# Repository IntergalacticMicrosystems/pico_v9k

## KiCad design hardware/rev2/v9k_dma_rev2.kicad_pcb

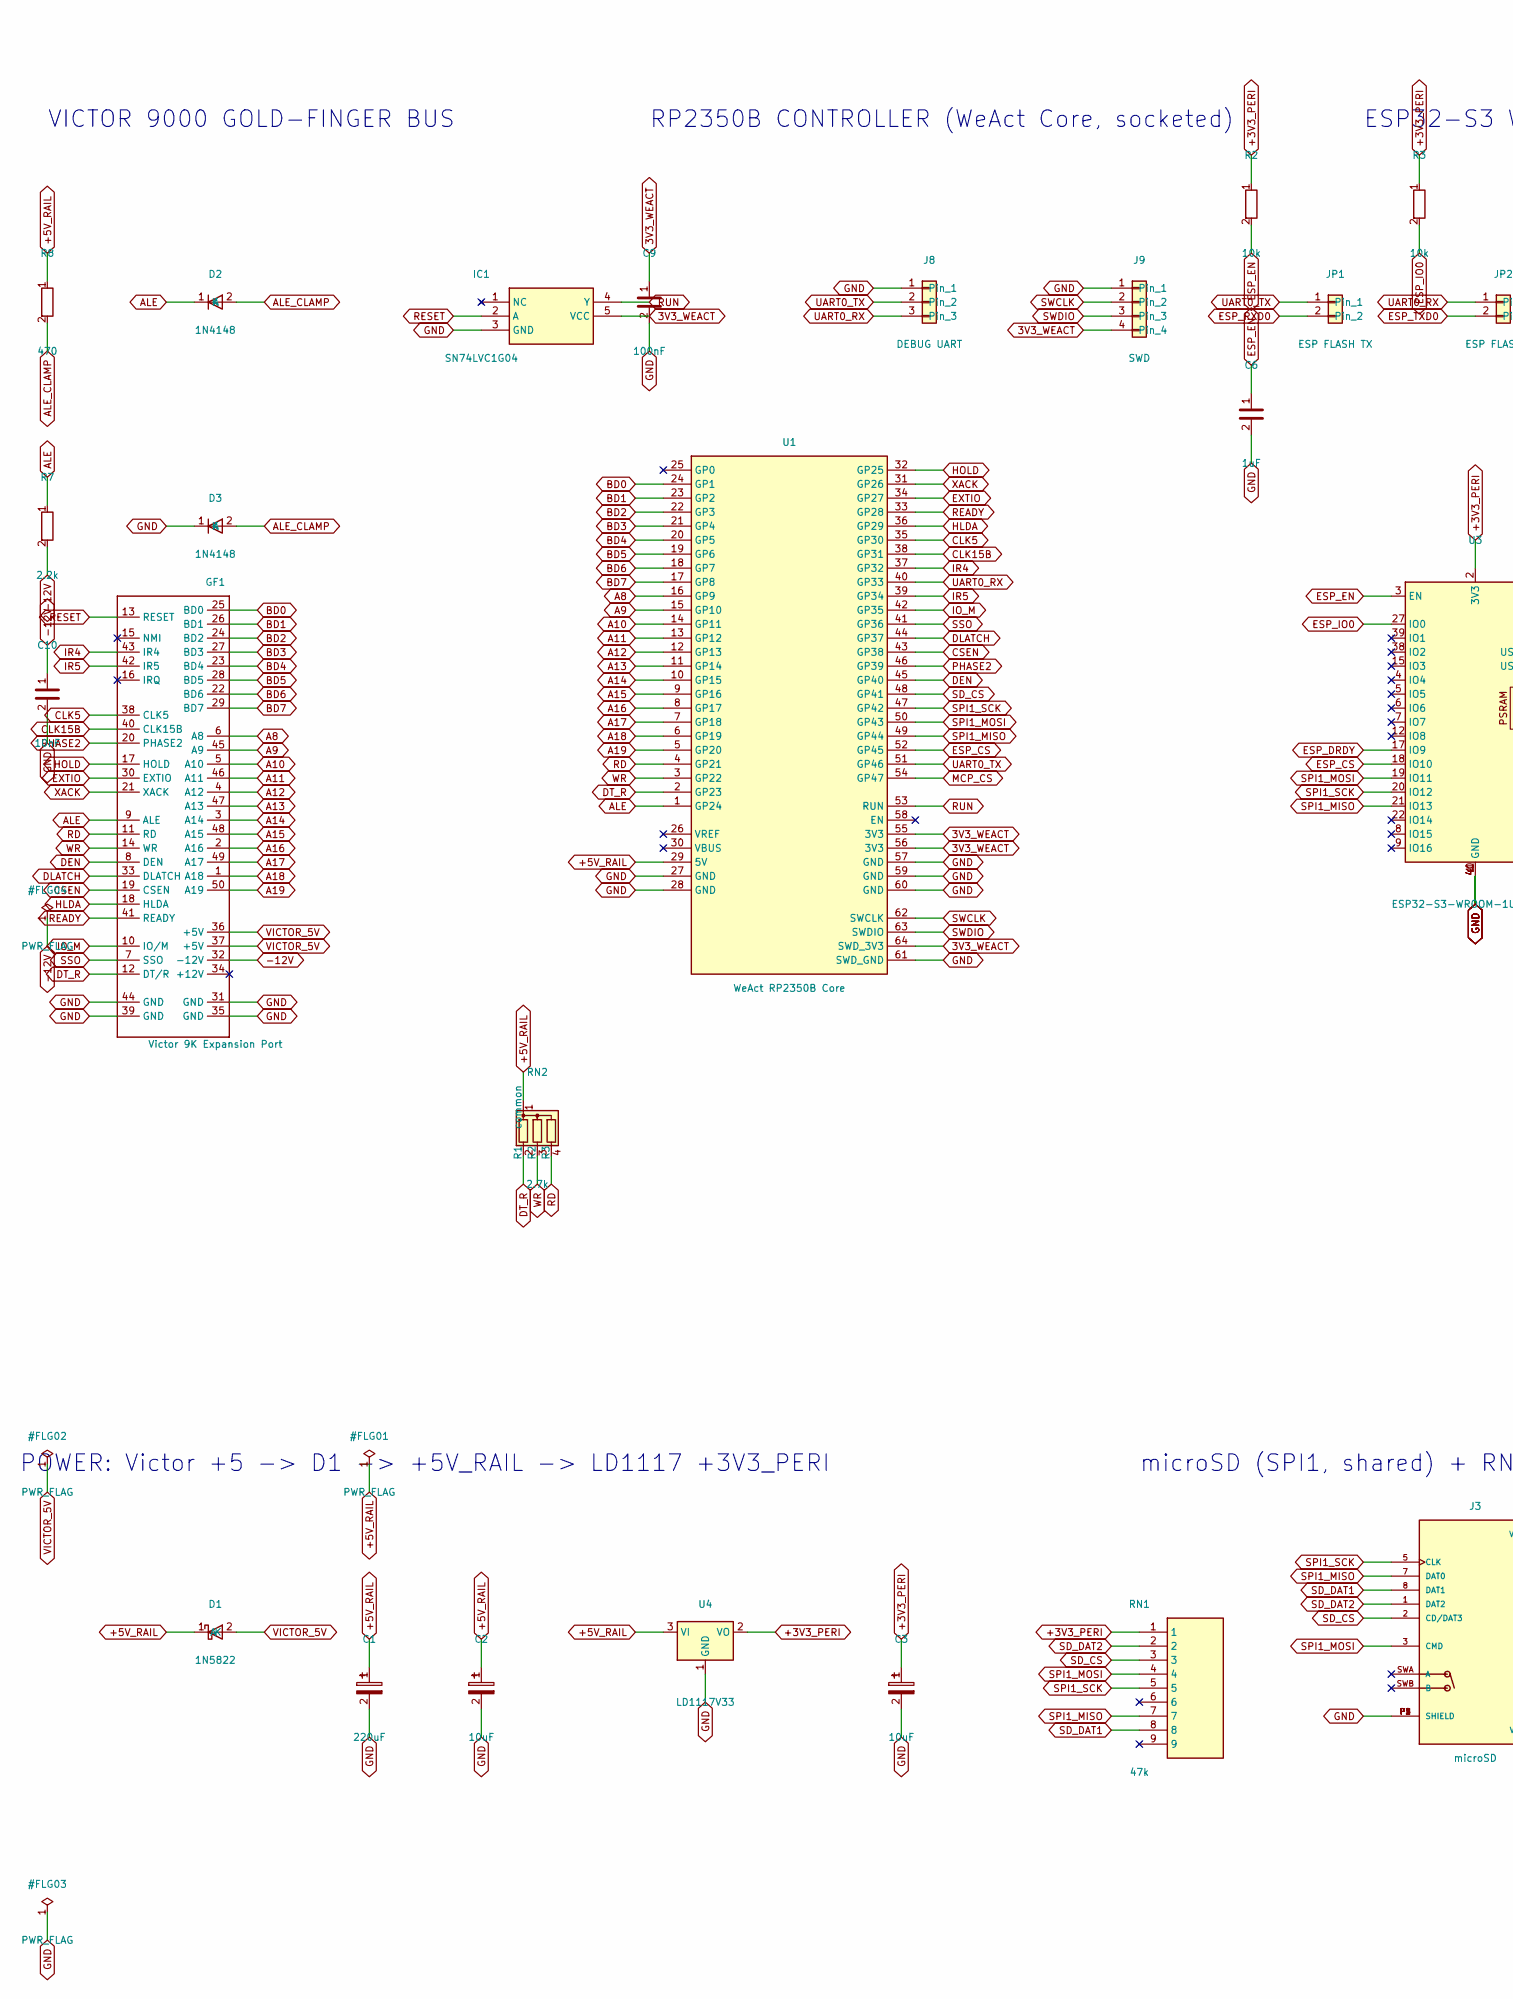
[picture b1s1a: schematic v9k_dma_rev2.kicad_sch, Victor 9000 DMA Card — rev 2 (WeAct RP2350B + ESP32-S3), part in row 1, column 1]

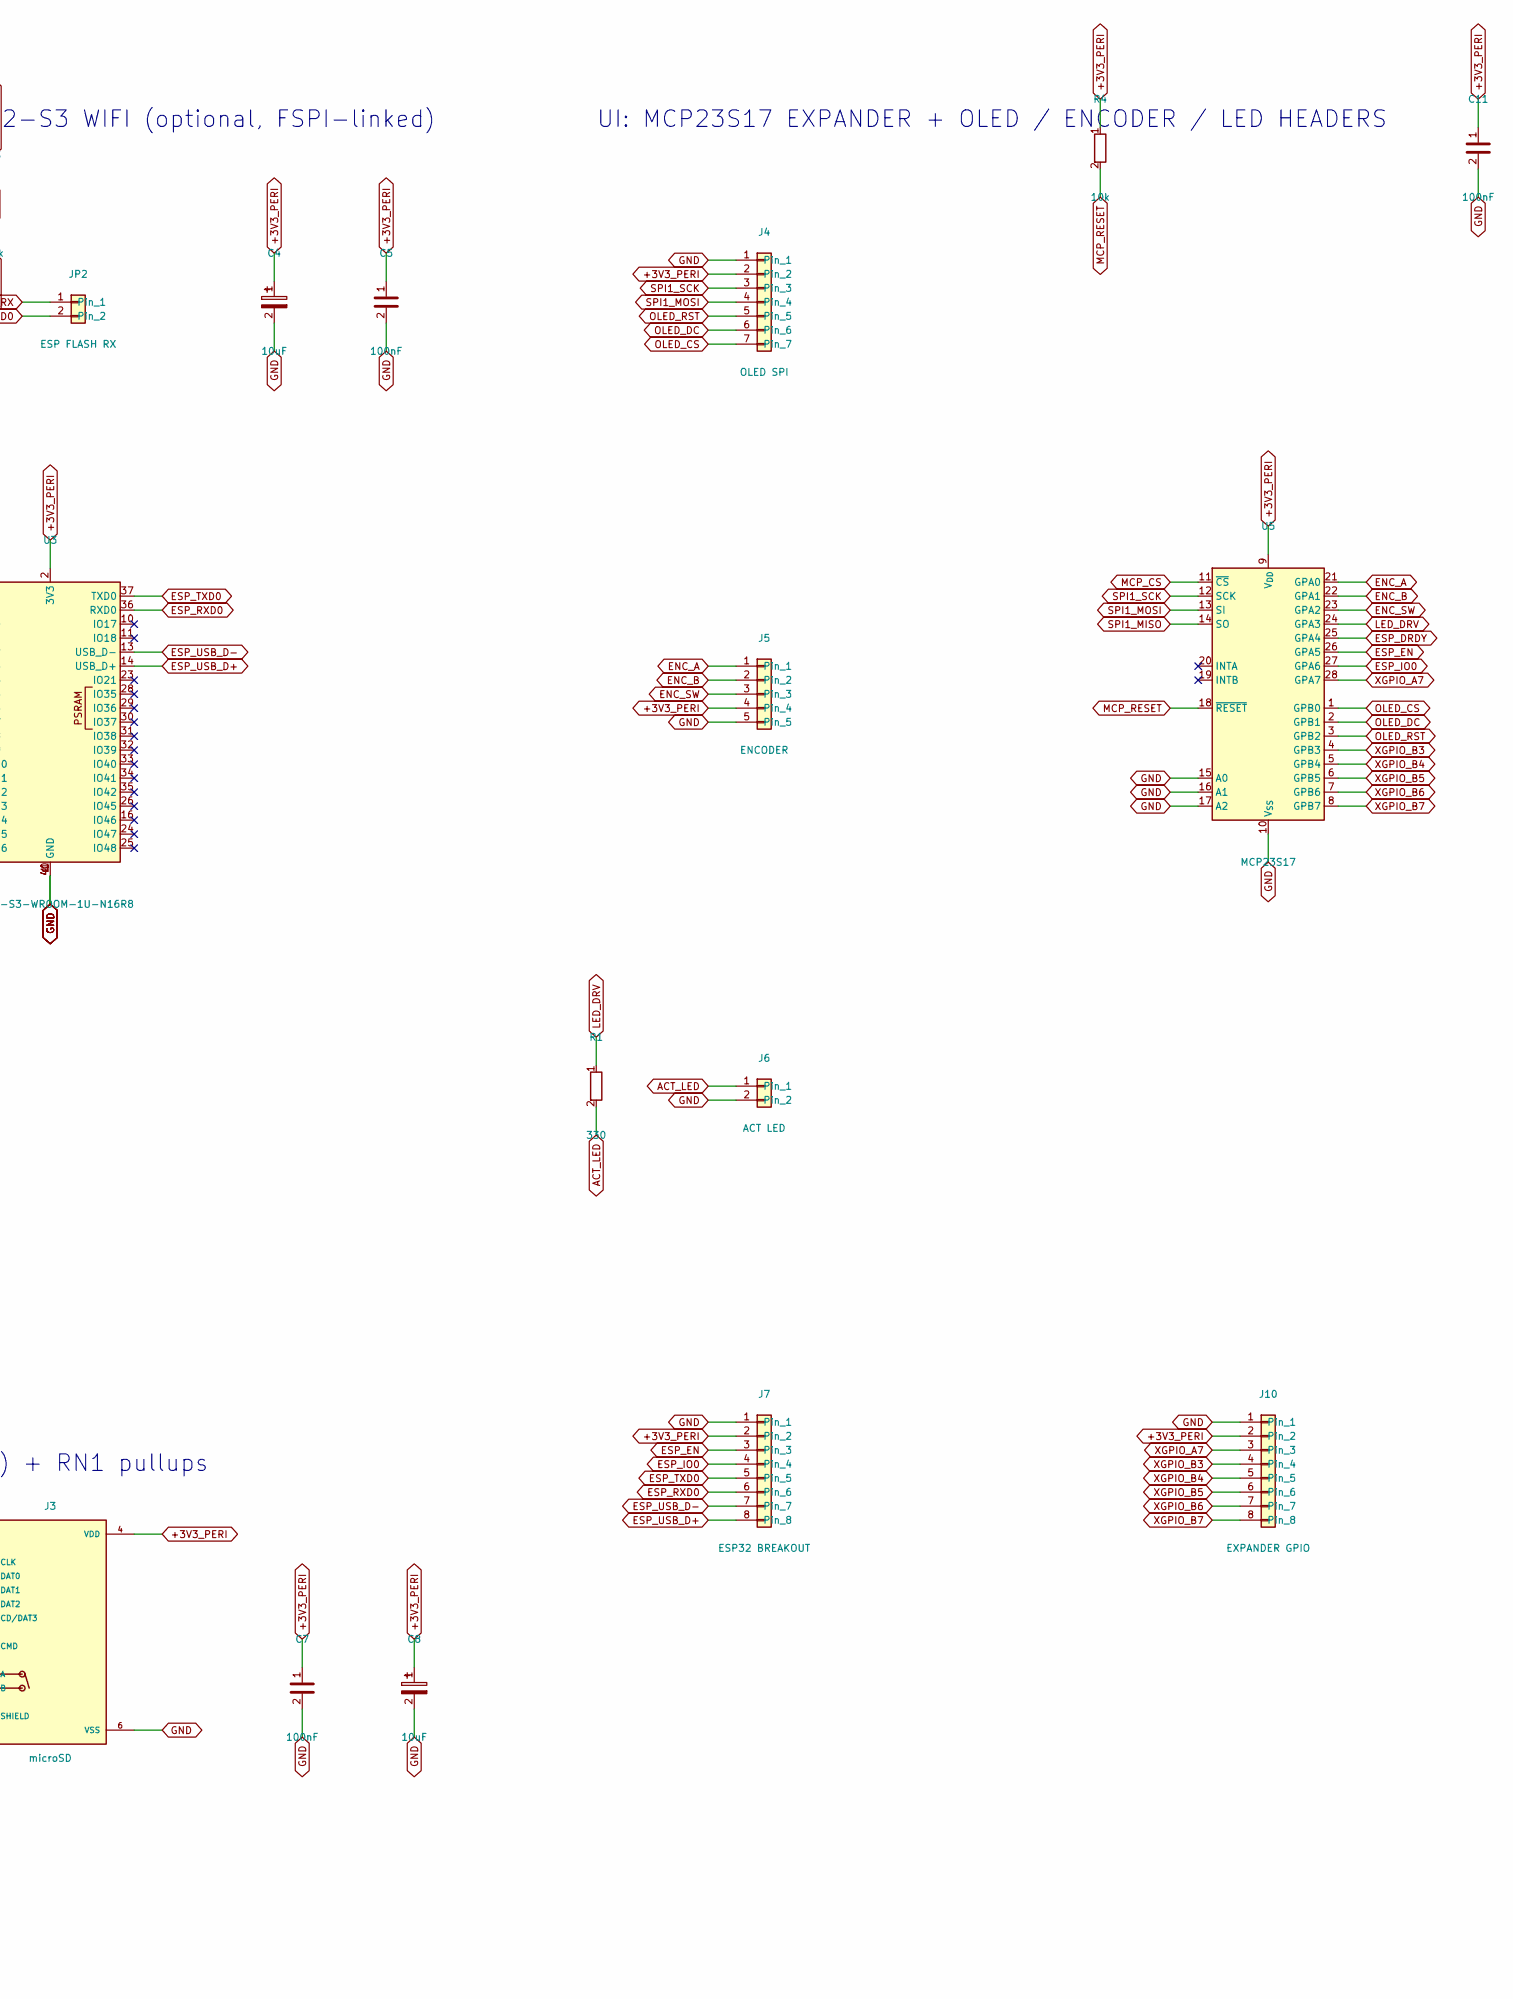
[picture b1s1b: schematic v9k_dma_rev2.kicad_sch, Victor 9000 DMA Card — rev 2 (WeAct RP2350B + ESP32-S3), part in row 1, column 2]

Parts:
C1: 220uF; CP_Radial_D8.0mm_P3.50mm; MPN ESE227M025AG3AA
C2, C3, C4, C8: 10uF; CP_Radial_D5.0mm_P2.00mm; MPN 50YXJ10M5X11
C5, C7, C9, C11: 100nF; C_Disc_D5.1mm_W3.2mm_P5.00mm; MPN RD20B104K500A5HAND
C6: 1uF; C_Disc_D5.1mm_W3.2mm_P5.00mm; MPN SR305E105ZARTR1
C10: 10nF; C_Disc_D5.0mm_W2.5mm_P2.50mm; MPN C315C103K5R5TA
D1: 1N5822; D_DO-201AD_P12.70mm_Horizontal; MPN 1N5822-TP
D2, D3: 1N4148; D_DO-35_SOD27_P7.62mm_Horizontal; MPN 1N4148
GF1: Victor 9K Expansion Port; Victor_Gold_Fingers_3
IC1: SN74LVC1G04; SOT65P210X110-5N; MPN SN74LVC1G04DCKR
J3: microSD; HRS_DM3AT-SF-PEJM5; MPN DM3AT-SF-PEJM5
J4: OLED SPI; PinHeader_1x07_P2.54mm_Vertical; MPN PREC040SAAN-RC
J5: ENCODER; PinHeader_1x05_P2.54mm_Vertical; MPN PREC040SAAN-RC
J6: ACT LED; PinHeader_1x02_P2.54mm_Vertical; MPN PREC040SAAN-RC
J7: ESP32 BREAKOUT; PinHeader_1x08_P2.54mm_Vertical; MPN PREC040SAAN-RC
J8: DEBUG UART; PinHeader_1x03_P2.54mm_Vertical; MPN PREC040SAAN-RC
J9: SWD; PinHeader_1x04_P2.54mm_Vertical; MPN PREC040SAAN-RC
J10: EXPANDER GPIO; PinHeader_1x08_P2.54mm_Vertical; MPN PREC040SAAN-RC
JP1: ESP FLASH TX; PinHeader_1x02_P2.54mm_Vertical; MPN PREC040SAAN-RC
JP2: ESP FLASH RX; PinHeader_1x02_P2.54mm_Vertical; MPN PREC040SAAN-RC
R1: 330; R_Axial_DIN0207_L6.3mm_D2.5mm_P7.62mm_Horizontal; MPN RNMF14FTC330R
R2, R3, R4: 10k; R_Axial_DIN0207_L6.3mm_D2.5mm_P7.62mm_Horizontal; MPN MFR-25FRF52-10K
R7: 2.2k; R_Axial_DIN0207_L6.3mm_D2.5mm_P7.62mm_Horizontal; MPN MFR-25FTE52-2K2
R8: 470; R_Axial_DIN0207_L6.3mm_D2.5mm_P7.62mm_Horizontal; MPN MFR-25FTE52-470R
RN1: 47k; 4609X101473LF; MPN 4609X-101-473LF
RN2: 2.7k; R_Array_SIP4; MPN 4604X-101-272LF
U1: WeAct RP2350B Core; WeAct_RP2350B_Core_Socket; MPN WeAct RP2350B Core Board (16MB flash + 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
U3: ESP32-S3-WROOM-1U-N16R8; ESP32-S3-WROOM-1U; MPN ESP32-S3-WROOM-1U-N16R8
U4: LD1117V33; TO-220-3_Vertical; MPN LD1117V33
U5: MCP23S17; DIP-28_W7.62mm; MPN MCP23S17-E/SP

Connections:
3V3_WEACT: C9.1, IC1.5 (VCC), J9.4, U1.55 (3V3), U1.56 (3V3), U1.64 (SWD_3V3)
+3V3_PERI: C3.1, C4.1, C5.1, C7.1, C8.1, C11.1, J3.4 (VDD), J4.2, J5.4, J7.2, J10.2, R2.1, R3.1, R4.1, RN1.1, U3.2 (3V3), U4.2 (VO), U5.9 (V_{DD})
+5V_RAIL: C1.1, C2.1, D1.1 (K), R8.1, RN2.1 (common), U1.29 (5V), U4.3 (VI)
-12V: C10.1, GF1.32 (-12V), R7.2
A8: GF1.6 (A8), U1.16 (GP9)
A9: GF1.45 (A9), U1.15 (GP10)
A10: GF1.5 (A10), U1.14 (GP11)
A11: GF1.46 (A11), U1.13 (GP12)
A12: GF1.4 (A12), U1.12 (GP13)
A13: GF1.47 (A13), U1.11 (GP14)
A14: GF1.3 (A14), U1.10 (GP15)
A15: GF1.48 (A15), U1.9 (GP16)
A16: GF1.2 (A16), U1.8 (GP17)
A17: GF1.49 (A17), U1.7 (GP18)
A18: GF1.1 (A18), U1.6 (GP19)
A19: GF1.50 (A19), U1.5 (GP20)
ACT_LED: J6.1, R1.2
ALE: D2.1 (K), GF1.9 (ALE), R7.1, U1.1 (GP24)
ALE_CLAMP: D2.2 (A), D3.2 (A), R8.2
BD0: GF1.25 (BD0), U1.24 (GP1)
BD1: GF1.26 (BD1), U1.23 (GP2)
BD2: GF1.24 (BD2), U1.22 (GP3)
BD3: GF1.27 (BD3), U1.21 (GP4)
BD4: GF1.23 (BD4), U1.20 (GP5)
BD5: GF1.28 (BD5), U1.19 (GP6)
BD6: GF1.22 (BD6), U1.18 (GP7)
BD7: GF1.29 (BD7), U1.17 (GP8)
CLK5: GF1.38 (CLK5), U1.35 (GP30)
CLK15B: GF1.40 (CLK15B), U1.38 (GP31)
CSEN: GF1.19 (CSEN), U1.43 (GP38)
DEN: GF1.8 (DEN), U1.45 (GP40)
DLATCH: GF1.33 (DLATCH), U1.44 (GP37)
DT_R: GF1.12 (DT/R), RN2.2 (R1), U1.2 (GP23)
ENC_A: J5.1, U5.21 (GPA0)
ENC_B: J5.2, U5.22 (GPA1)
ENC_SW: J5.3, U5.23 (GPA2)
ESP_CS: U1.52 (GP45), U3.18 (IO10)
ESP_DRDY: U3.17 (IO9), U5.25 (GPA4)
ESP_EN: C6.1, J7.3, R2.2, U3.3 (EN), U5.26 (GPA5)
ESP_IO0: J7.4, R3.2, U3.27 (IO0), U5.27 (GPA6)
ESP_RXD0: J7.6, JP1.2, U3.36 (RXD0)
ESP_TXD0: J7.5, JP2.2, U3.37 (TXD0)
ESP_USB_D+: J7.8, U3.14 (USB_D+)
ESP_USB_D-: J7.7, U3.13 (USB_D-)
EXTIO: GF1.30 (EXTIO), U1.34 (GP27)
GND: C1.2, C2.2, C3.2, C4.2, C5.2, C6.2, C7.2, C8.2, C9.2, C10.2, C11.2, D3.1 (K), GF1.31 (GND), GF1.35 (GND), GF1.39 (GND), GF1.44 (GND), IC1.3 (GND), J3.6 (VSS), J3.P1 (SHIELD), J3.P2 (SHIELD), J3.P3 (SHIELD), J3.P4 (SHIELD), J4.1, J5.5, J6.2, J7.1, J8.1, J9.1, J10.1, U1.27 (GND), U1.28 (GND), U1.57 (GND), U1.59 (GND), U1.60 (GND), U1.61 (SWD_GND), U3.1 (GND), U3.40 (GND), U3.41 (GND), U4.1 (GND), U5.10 (V_{SS}), U5.15 (A0), U5.16 (A1), U5.17 (A2)
HLDA: GF1.18 (HLDA), U1.36 (GP29)
HOLD: GF1.17 (HOLD), U1.32 (GP25)
IO_M: GF1.10 (IO/M), U1.42 (GP35)
IR4: GF1.43 (IR4), U1.37 (GP32)
IR5: GF1.42 (IR5), U1.39 (GP34)
LED_DRV: R1.1, U5.24 (GPA3)
MCP_CS: U1.54 (GP47), U5.11 (~CS)
MCP_RESET: R4.2, U5.18 (~RESET)
OLED_CS: J4.7, U5.1 (GPB0)
OLED_DC: J4.6, U5.2 (GPB1)
OLED_RST: J4.5, U5.3 (GPB2)
PHASE2: GF1.20 (PHASE2), U1.46 (GP39)
RD: GF1.11 (RD), RN2.4 (R3), U1.4 (GP21)
READY: GF1.41 (READY), U1.33 (GP28)
RESET: GF1.13 (RESET), IC1.2 (A)
RUN: IC1.4 (Y), U1.53 (RUN)
SD_CS: J3.2 (CD/DAT3), RN1.3, U1.48 (GP41)
SD_DAT1: J3.8 (DAT1), RN1.8
SD_DAT2: J3.1 (DAT2), RN1.2
SPI1_MISO: J3.7 (DAT0), RN1.7, U1.49 (GP44), U3.21 (IO13), U5.14 (SO)
SPI1_MOSI: J3.3 (CMD), J4.4, RN1.4, U1.50 (GP43), U3.19 (IO11), U5.13 (SI)
SPI1_SCK: J3.5 (CLK), J4.3, RN1.5, U1.47 (GP42), U3.20 (IO12), U5.12 (SCK)
SSO: GF1.7 (SSO), U1.41 (GP36)
SWCLK: J9.2, U1.62 (SWCLK)
SWDIO: J9.3, U1.63 (SWDIO)
UART0_RX: J8.3, JP2.1, U1.40 (GP33)
UART0_TX: J8.2, JP1.1, U1.51 (GP46)
VICTOR_5V: D1.2 (A), GF1.36 (+5V), GF1.37 (+5V)
WR: GF1.14 (WR), RN2.3 (R2), U1.3 (GP22)
XACK: GF1.21 (XACK), U1.31 (GP26)
XGPIO_A7: J10.3, U5.28 (GPA7)
XGPIO_B3: J10.4, U5.4 (GPB3)
XGPIO_B4: J10.5, U5.5 (GPB4)
XGPIO_B5: J10.6, U5.6 (GPB5)
XGPIO_B6: J10.7, U5.7 (GPB6)
XGPIO_B7: J10.8, U5.8 (GPB7)

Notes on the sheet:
VICTOR 9000 GOLD-FINGER BUS
RP2350B CONTROLLER (WeAct Core, socketed)
ESP32-S3 WIFI (optional, FSPI-linked)
POWER: Victor +5 -> D1 -> +5V_RAIL -> LD1117 +3V3_PERI
microSD (SPI1, shared) + RN1 pullups
UI: MCP23S17 EXPANDER + OLED / ENCODER / LED HEADERS

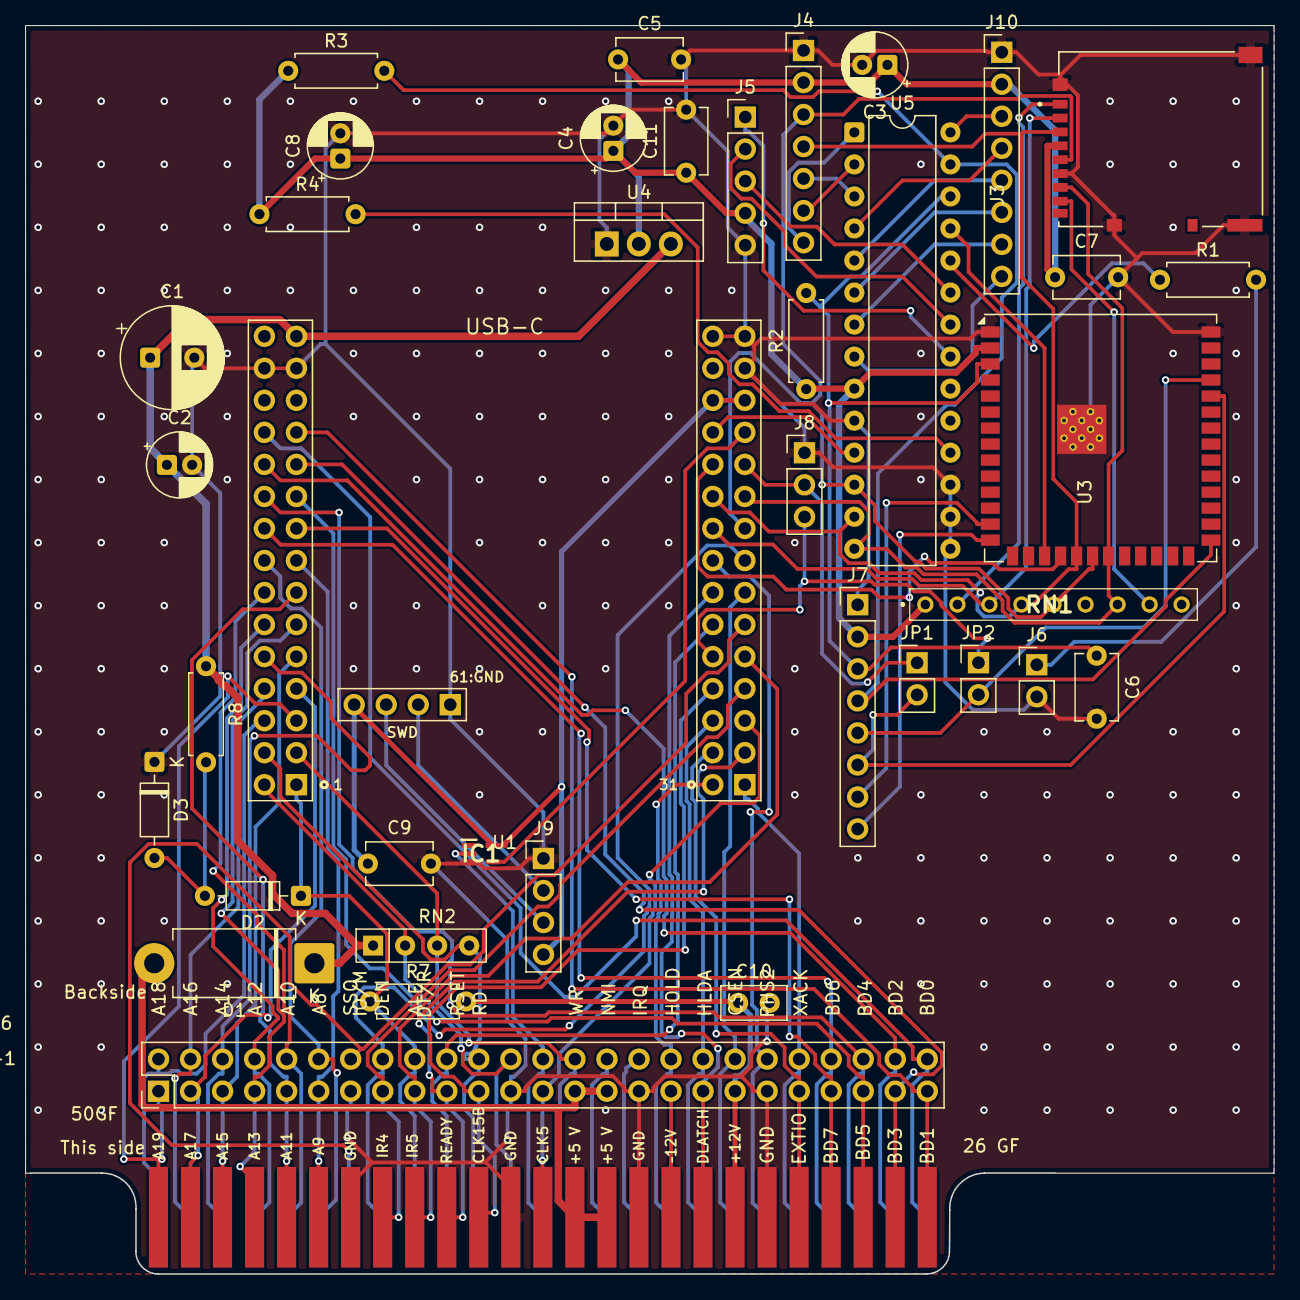
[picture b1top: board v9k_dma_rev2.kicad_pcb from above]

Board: 2 copper layers, 99.0 x 99.0 mm, 38 parts (0 on the bottom side), 82 nets.

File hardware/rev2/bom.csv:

"Reference","Value","Footprint","Qty","DNP","MPN","LCSC"
"C1","220uF","Capacitor_THT:CP_Radial_D8.0mm_P3.50mm","1","","ESE227M025AG3AA",""
"C2","10uF","Capacitor_THT:CP_Radial_D5.0mm_P2.00mm","1","","50YXJ10M5X11",""
"C3","10uF","Capacitor_THT:CP_Radial_D5.0mm_P2.00mm","1","","50YXJ10M5X11",""
"C4","10uF","Capacitor_THT:CP_Radial_D5.0mm_P2.00mm","1","","50YXJ10M5X11",""
"C5","100nF","Capacitor_THT:C_Disc_D5.1mm_W3.2mm_P5.00mm","1","","RD20B104K500A5HAND",""
"C6","1uF","Capacitor_THT:C_Disc_D5.1mm_W3.2mm_P5.00mm","1","","SR305E105ZARTR1",""
"C7","100nF","Capacitor_THT:C_Disc_D5.1mm_W3.2mm_P5.00mm","1","","RD20B104K500A5HAND",""
"C8","10uF","Capacitor_THT:CP_Radial_D5.0mm_P2.00mm","1","","50YXJ10M5X11",""
"C9","100nF","Capacitor_THT:C_Disc_D5.1mm_W3.2mm_P5.00mm","1","","RD20B104K500A5HAND",""
"C10","10nF","Capacitor_THT:C_Disc_D5.0mm_W2.5mm_P2.50mm","1","","C315C103K5R5TA",""
"C11","100nF","Capacitor_THT:C_Disc_D5.1mm_W3.2mm_P5.00mm","1","","RD20B104K500A5HAND",""
"D1","1N5822","Diode_THT:D_DO-201AD_P12.70mm_Horizontal","1","","1N5822-TP",""
"D2","1N4148","Diode_THT:D_DO-35_SOD27_P7.62mm_Horizontal","1","","1N4148",""
"D3","1N4148","Diode_THT:D_DO-35_SOD27_P7.62mm_Horizontal","1","","1N4148",""
"IC1","SN74LVC1G04","v9k_dma_rev2:SOT65P210X110-5N","1","","SN74LVC1G04DCKR",""
"J3","microSD","v9k_dma_rev2:HRS_DM3AT-SF-PEJM5","1","","DM3AT-SF-PEJM5",""
"J4","OLED SPI","Connector_PinHeader_2.54mm:PinHeader_1x07_P2.54mm_Vertical","1","","PREC040SAAN-RC",""
"J5","ENCODER","Connector_PinHeader_2.54mm:PinHeader_1x05_P2.54mm_Vertical","1","","PREC040SAAN-RC",""
"J6","ACT LED","Connector_PinHeader_2.54mm:PinHeader_1x02_P2.54mm_Vertical","1","","PREC040SAAN-RC",""
"J7","ESP32 BREAKOUT","Connector_PinHeader_2.54mm:PinHeader_1x08_P2.54mm_Vertical","1","","PREC040SAAN-RC",""
"J8","DEBUG UART","Connector_PinHeader_2.54mm:PinHeader_1x03_P2.54mm_Vertical","1","","PREC040SAAN-RC",""
"J9","SWD","Connector_PinHeader_2.54mm:PinHeader_1x04_P2.54mm_Vertical","1","","PREC040SAAN-RC",""
"J10","EXPANDER GPIO","Connector_PinHeader_2.54mm:PinHeader_1x08_P2.54mm_Vertical","1","","PREC040SAAN-RC",""
"JP1","ESP FLASH TX","Connector_PinHeader_2.54mm:PinHeader_1x02_P2.54mm_Vertical","1","","PREC040SAAN-RC",""
"JP2","ESP FLASH RX","Connector_PinHeader_2.54mm:PinHeader_1x02_P2.54mm_Vertical","1","","PREC040SAAN-RC",""
"R1","330","Resistor_THT:R_Axial_DIN0207_L6.3mm_D2.5mm_P7.62mm_Horizontal","1","","RNMF14FTC330R",""
"R2","10k","Resistor_THT:R_Axial_DIN0207_L6.3mm_D2.5mm_P7.62mm_Horizontal","1","","MFR-25FRF52-10K",""
"R3","10k","Resistor_THT:R_Axial_DIN0207_L6.3mm_D2.5mm_P7.62mm_Horizontal","1","","MFR-25FRF52-10K",""
"R4","10k","Resistor_THT:R_Axial_DIN0207_L6.3mm_D2.5mm_P7.62mm_Horizontal","1","","MFR-25FRF52-10K",""
"R7","2.2k","Resistor_THT:R_Axial_DIN0207_L6.3mm_D2.5mm_P7.62mm_Horizontal","1","","MFR-25FTE52-2K2",""
"R8","470","Resistor_THT:R_Axial_DIN0207_L6.3mm_D2.5mm_P7.62mm_Horizontal","1","","MFR-25FTE52-470R",""
"RN1","47k","v9k_dma_rev2:4609X101473LF","1","","4609X-101-473LF",""
"RN2","2.7k","Resistor_THT:R_Array_SIP4","1","","4604X-101-272LF",""
"U3","ESP32-S3-WROOM-1U-N16R8","RF_Module:ESP32-S3-WROOM-1U","1","","ESP32-S3-WROOM-1U-N16R8",""
"U4","LD1117V33","Package_TO_SOT_THT:TO-220-3_Vertical","1","","LD1117V33",""
"U5","MCP23S17","Package_DIP:DIP-28_W7.62mm","1","","MCP23S17-E/SP",""

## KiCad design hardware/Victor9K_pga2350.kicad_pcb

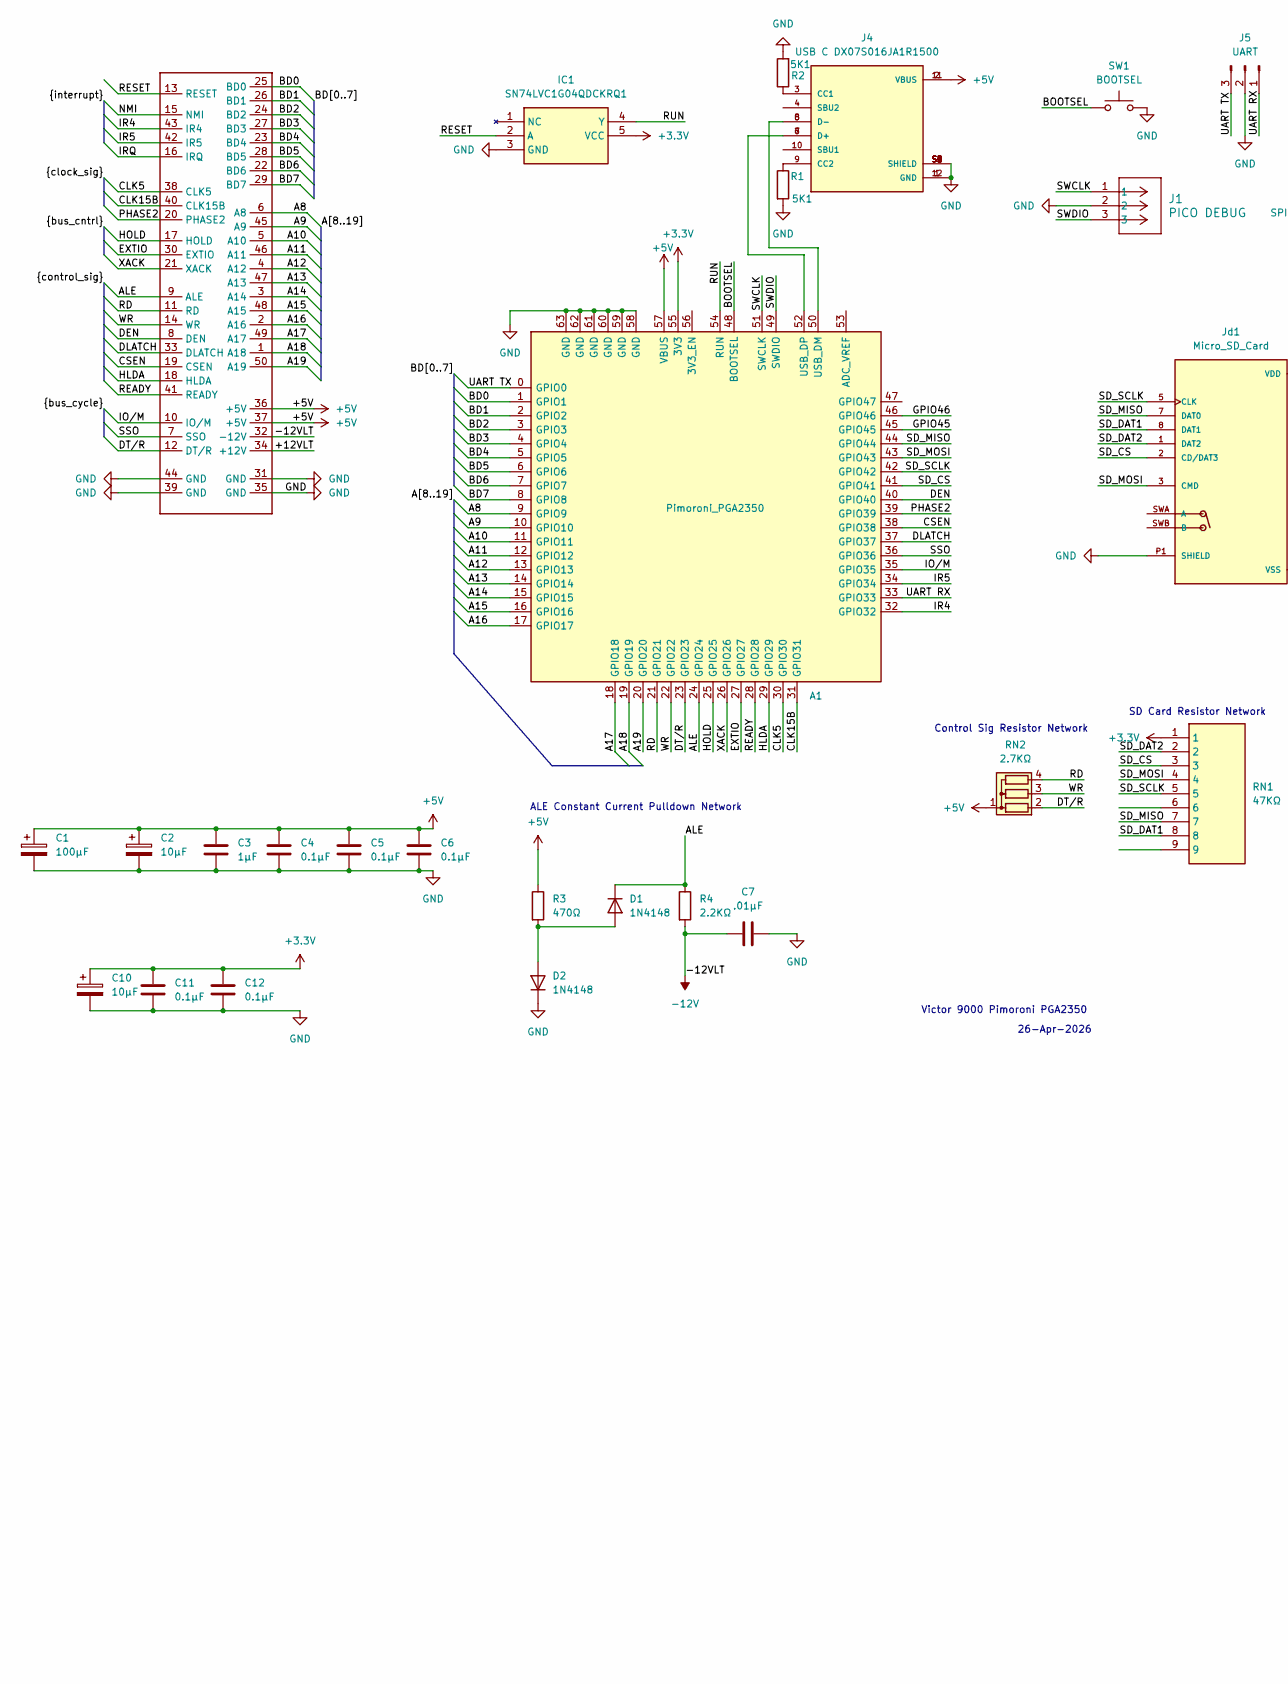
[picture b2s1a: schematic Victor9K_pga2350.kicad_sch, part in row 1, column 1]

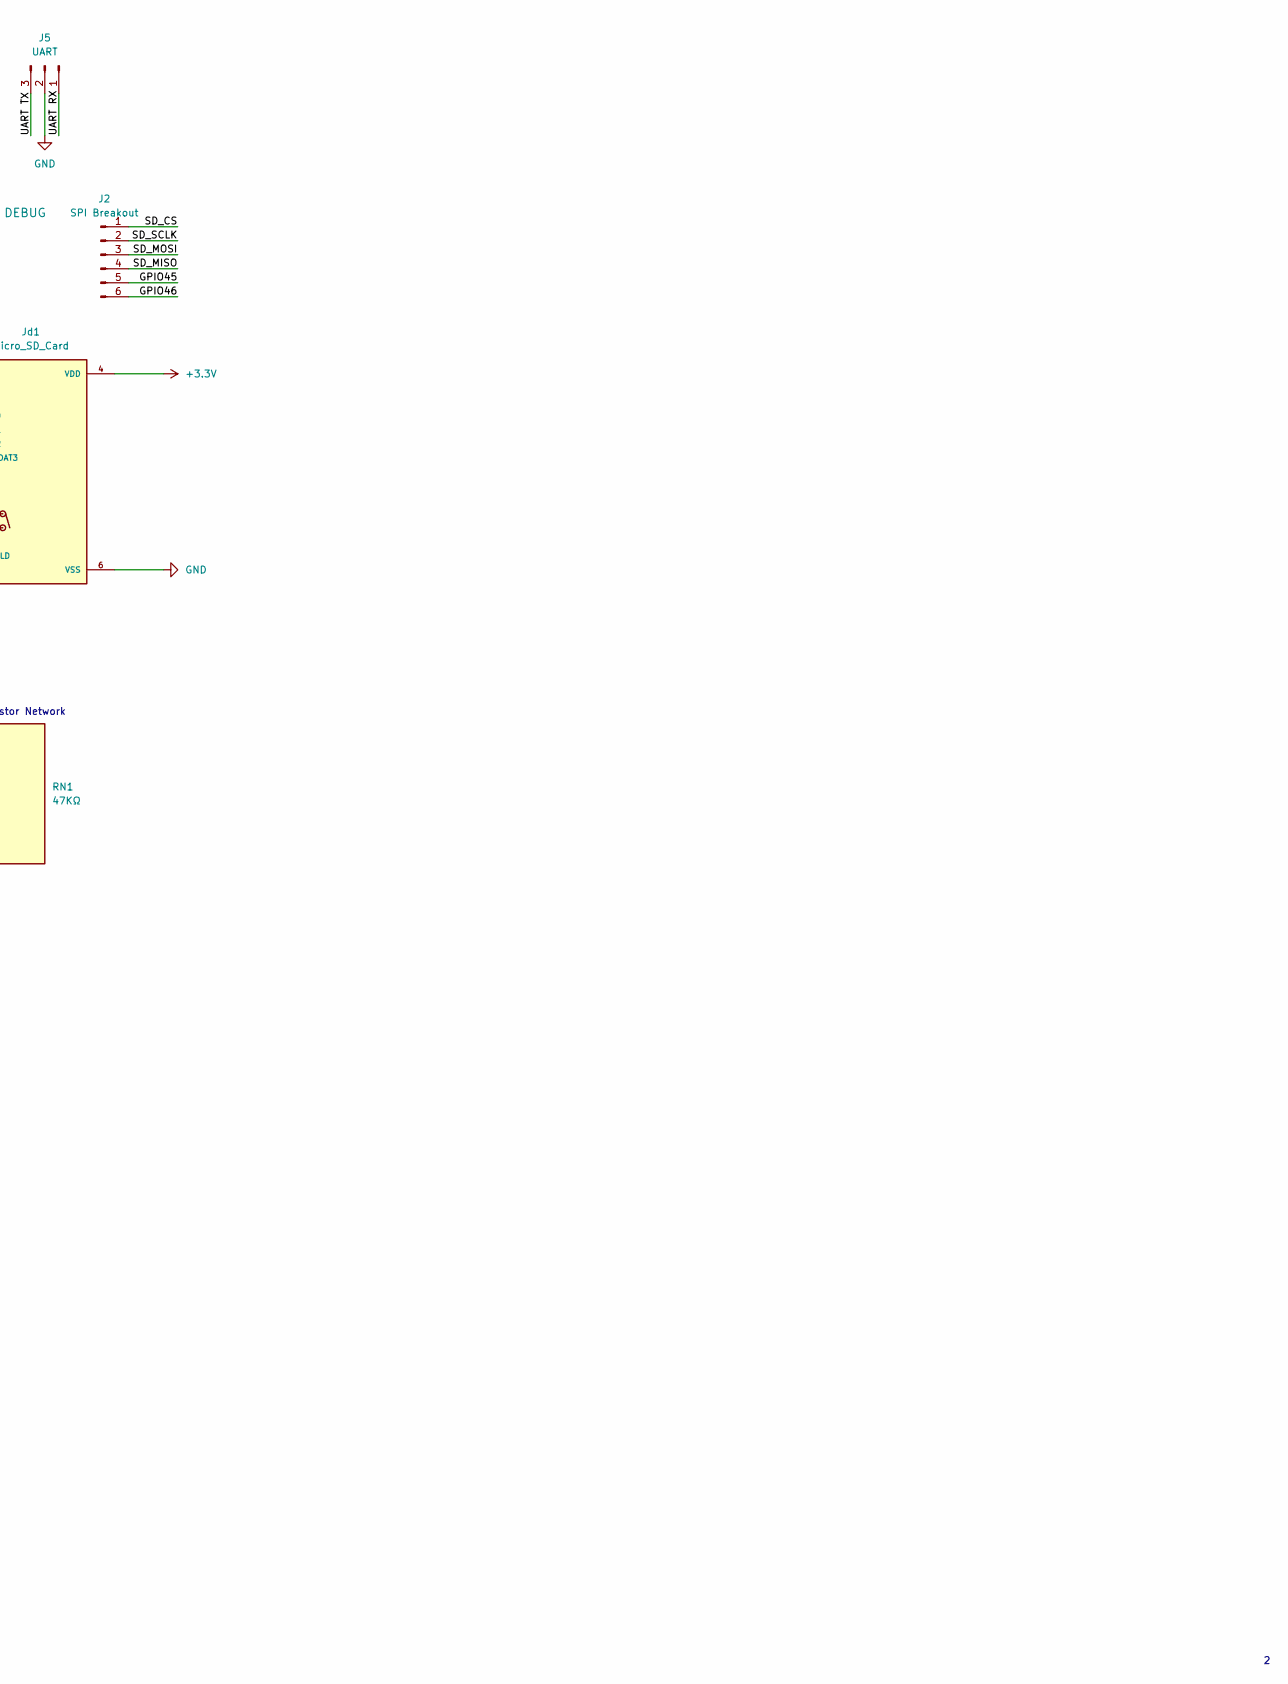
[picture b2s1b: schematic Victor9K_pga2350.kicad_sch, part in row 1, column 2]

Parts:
A1: Pimoroni_PGA2350; pimoroni_pga2350
C1: 100µF; CP_Axial_L11.0mm_D8.0mm_P15.00mm_Horizontal
C2, C10: 10µF; C_Disc_D5.0mm_W2.5mm_P5.00mm
C3: 1µF; C_Disc_D5.0mm_W2.5mm_P5.00mm
C4, C5, C6, C11, C12: 0.1µF; C_Disc_D5.0mm_W2.5mm_P5.00mm
C7: .01µF; C_Disc_D5.0mm_W2.5mm_P5.00mm
D1, D2: 1N4148; D_DO-35_SOD27_P7.62mm_Horizontal
GF1: Victor 9K Expansion Port; Victor_Gold_Fingers_3
IC1: SN74LVC1G04QDCKRQ1; SOT65P210X110-5N; Mouser Part Number 595-SN74LVC1G04QDCQ1
J1: PICO DEBUG; CONN_BM03B-SRSS-TBLFSN_JST
J2: SPI Breakout; PinHeader_1x06_P2.54mm_Vertical
J4: USB C DX07S016JA1R1500; JAE_DX07S016JA1R1500; PARTREV 1; JLCPCB Part # C3197885
J5: UART; PinHeader_1x03_P2.54mm_Vertical
Jd1: Micro_SD_Card; HRS_DM3AT-SF-PEJM5; PARTREV 20200913
R1, R2: 5K1; R_Axial_DIN0204_L3.6mm_D1.6mm_P5.08mm_Horizontal
R3: 470Ω; R_Axial_DIN0204_L3.6mm_D1.6mm_P5.08mm_Horizontal
R4: 2.2KΩ; R_Axial_DIN0204_L3.6mm_D1.6mm_P5.08mm_Horizontal
RN1: 47KΩ; 4609X101473LF; Mouser Part Number 652-4609X-1LF-47K
RN2: 2.7KΩ; R_Array_SIP4
SW1: BOOTSEL; B3FS1010P

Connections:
+3.3V: A1.55 (3V3), C10.1, C11.1, C12.1, IC1.5 (VCC), Jd1.4 (VDD), RN1.1
+5V: A1.57 (VBUS), C1.1, C2.1, C3.1, C4.1, C5.1, C6.1, GF1.36 (+5V), GF1.37 (+5V), J4.2 (VBUS), J4.11 (VBUS), R3.1, RN2.1 (common)
-12V: C7.1, GF1.32 (-12V), R4.2
/+12VLT: GF1.34 (+12V)
/A8: A1.9 (GPIO9), GF1.6 (A8)
/A9: A1.10 (GPIO10), GF1.45 (A9)
/A10: A1.11 (GPIO11), GF1.5 (A10)
/A11: A1.12 (GPIO12), GF1.46 (A11)
/A12: A1.13 (GPIO13), GF1.4 (A12)
/A13: A1.14 (GPIO14), GF1.47 (A13)
/A14: A1.15 (GPIO15), GF1.3 (A14)
/A15: A1.16 (GPIO16), GF1.48 (A15)
/A16: A1.17 (GPIO17), GF1.2 (A16)
/A17: A1.18 (GPIO18), GF1.49 (A17)
/A18: A1.19 (GPIO19), GF1.1 (A18)
/A19: A1.20 (GPIO20), GF1.50 (A19)
/ALE: A1.24 (GPIO24), D1.1 (K), GF1.9 (ALE), R4.1
/BD0: A1.1 (GPIO1), GF1.25 (BD0)
/BD1: A1.2 (GPIO2), GF1.26 (BD1)
/BD2: A1.3 (GPIO3), GF1.24 (BD2)
/BD3: A1.4 (GPIO4), GF1.27 (BD3)
/BD4: A1.5 (GPIO5), GF1.23 (BD4)
/BD5: A1.6 (GPIO6), GF1.28 (BD5)
/BD6: A1.7 (GPIO7), GF1.22 (BD6)
/BD7: A1.8 (GPIO8), GF1.29 (BD7)
/BOOTSEL: A1.48 (BOOTSEL), SW1.1
/CLK5: A1.30 (GPIO30), GF1.38 (CLK5)
/CLK15B: A1.31 (GPIO31), GF1.40 (CLK15B)
/CSEN: A1.38 (GPIO38), GF1.19 (CSEN)
/DEN: A1.40 (GPIO40), GF1.8 (DEN)
/DLATCH: A1.37 (GPIO37), GF1.33 (DLATCH)
/DT/R: A1.23 (GPIO23), GF1.12 (DT/R), RN2.2 (R1)
/EXTIO: A1.27 (GPIO27), GF1.30 (EXTIO)
/GPIO45: A1.45 (GPIO45), J2.5
/GPIO46: A1.46 (GPIO46), J2.6
/HLDA: A1.29 (GPIO29), GF1.18 (HLDA)
/HOLD: A1.25 (GPIO25), GF1.17 (HOLD)
/IO/M: A1.35 (GPIO35), GF1.10 (IO/M)
/IR4: A1.32 (GPIO32), GF1.43 (IR4)
/IR5: A1.34 (GPIO34), GF1.42 (IR5)
/IRQ: GF1.16 (IRQ)
/NMI: GF1.15 (NMI)
/PHASE2: A1.39 (GPIO39), GF1.20 (PHASE2)
/RD: A1.21 (GPIO21), GF1.11 (RD), RN2.4 (R3)
/READY: A1.28 (GPIO28), GF1.41 (READY)
/RESET: GF1.13 (RESET), IC1.2 (A)
/RUN: A1.54 (RUN), IC1.4 (Y)
/SD_CS: A1.41 (GPIO41), J2.1, Jd1.2 (CD/DAT3), RN1.3
/SD_DAT1: Jd1.8 (DAT1), RN1.8
/SD_DAT2: Jd1.1 (DAT2), RN1.2
/SD_MISO: A1.44 (GPIO44), J2.4, Jd1.7 (DAT0), RN1.7
/SD_MOSI: A1.43 (GPIO43), J2.3, Jd1.3 (CMD), RN1.4
/SD_SCLK: A1.42 (GPIO42), J2.2, Jd1.5 (CLK), RN1.5
/SSO: A1.36 (GPIO36), GF1.7 (SSO)
/SWCLK: A1.51 (SWCLK), J1.1
/SWDIO: A1.49 (SWDIO), J1.3
/UART RX: A1.33 (GPIO33), J5.1
/UART TX: A1.0 (GPIO0), J5.3
/WR: A1.22 (GPIO22), GF1.14 (WR), RN2.3 (R2)
/XACK: A1.26 (GPIO26), GF1.21 (XACK)
GND: A1.58 (GND), A1.59 (GND), A1.60 (GND), A1.61 (GND), A1.62 (GND), A1.63 (GND), C1.2, C2.2, C3.2, C4.2, C5.2, C6.2, C7.2, C10.2, C11.2, C12.2, D2.1 (K), GF1.31 (GND), GF1.35 (GND), GF1.39 (GND), GF1.44 (GND), IC1.3 (GND), J1.2, J4.1 (GND), J4.12 (GND), J4.S1 (SHIELD), J4.S2 (SHIELD), J4.S3 (SHIELD), J4.S4 (SHIELD), J4.S5 (SHIELD), J4.S6 (SHIELD), J5.2, Jd1.6 (VSS), Jd1.P1 (SHIELD), Jd1.P2 (SHIELD), Jd1.P3 (SHIELD), Jd1.P4 (SHIELD), R1.2, R2.2, SW1.2
unnamed: A1.50 (USB_DM), J4.5 (D-), J4.8 (D-)
unnamed: A1.52 (USB_DP), J4.6 (D+), J4.7 (D+)
unnamed: D1.2 (A), D2.2 (A), R3.2
unnamed: J4.3 (CC1), R2.1
unnamed: J4.9 (CC2), R1.1

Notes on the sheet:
26-Apr-2026
Control Sig Resistor Network
SD Card Resistor Network
ALE Constant Current Pulldown Network
Victor 9000 Pimoroni PGA2350

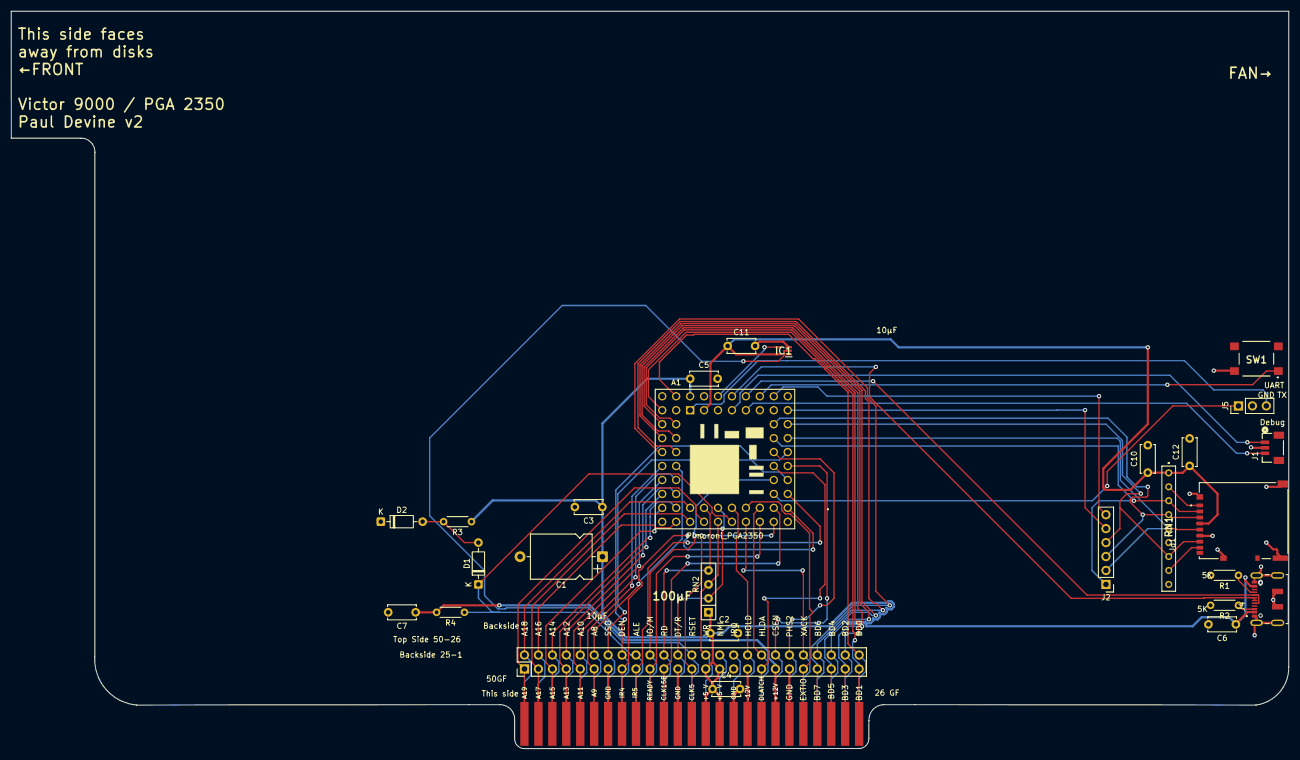
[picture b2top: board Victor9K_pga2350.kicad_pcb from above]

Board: 4 copper layers, 232.7 x 134.3 mm, 27 parts (0 on the bottom side), 63 nets.

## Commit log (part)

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2026-04-10 Stabilize DMA bus handoff
2026-04-19 lowering drive strength to reduce ringing when driving pins high
2026-04-19 added ALE pulldown circuit connected to GPIO 46.
2026-04-25 adjusted T cycle timing for faster iteration after fixing ALE circuit. set ALE drive strength to 12ma, rest of pins to 4ma.
2026-05-01 reworked PCB for latest gpio configuration. added reset connect to 8088, adjusted SIP for SD card instead of SDIO. added UART RX and SIP breakout pins.
